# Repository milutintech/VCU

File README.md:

# VCU - Vehicle Control Unit

A professional FreeRTOS-based vehicle control unit for ESP32-S3 with a JSON/WebSocket API. [LIVI](../../LIVI) is the user interface; the VCU serves no web page of its own.

## Features

### Core Functionality
- **FreeRTOS Multi-tasking**: Three dedicated tasks for CAN communication, control logic, and web server
- **Advanced Pedal Control**: Three-zone system (Regen/Coast/Accel) with smooth torque transitions
- **CAN Bus Integration**: Manages BMS, DMC, BSC, and NLG subsystems
- **Persistent Configuration**: JSON-based flash storage with validation
- **Real-time Monitoring**: Error logging, performance metrics, and system health checks

### API
- **Always-On Web Server**: REST + WebSocket on port 80, used by LIVI
- **WebSocket Updates**: 10Hz live data streaming
- **BMS cells and faults**: see the end of this file

## Hardware

### Microcontroller
- **ESP32-S3 DevKit C1**
- Dual-core ARM @ 240 MHz
- 16 MB Flash, 8 MB SRAM

### Communication
- MCP2515 CAN Controller (SPI)
- ADS1115 16-bit ADC (I2C)
- WiFi 802.11 b/g/n

### I/O
- Dual throttle pedal inputs
- HV contactor control
- Cooling pump PWM
- Charger/inverter enable outputs
- Connector unlock interrupt

## Quick Start

### 1. Build and Upload Firmware

```bash
# Install PlatformIO
pip install platformio

# Build project
pio run

# Upload firmware
pio run --target upload
```

### 2. First-Time Setup

1. Power on the VCU
2. Look for WiFi network: `VCU_XXXXX` (XXXXX = chip ID)
3. Connect with password: `vcu12345`
4. Point LIVI at `192.168.4.1` (Settings → Vehicle → Status)

## REST API

All configuration is accessible via REST API:

### Status Endpoints
```
GET /api/status              - System status
GET /api/status/live         - Real-time vehicle data
GET /api/status/errors       - Error log
```

### Configuration Endpoints
```
GET  /api/config/driving     - Get driving config
POST /api/config/driving     - Set driving config
GET  /api/config/charging    - Get charging config
POST /api/config/charging    - Set charging config
GET  /api/config/pedal       - Get pedal zones
POST /api/config/pedal       - Set pedal zones
GET  /api/config/transition  - Get torque transitions
POST /api/config/transition  - Set torque transitions
GET  /api/config/limits      - Get speed/power limits
POST /api/config/limits      - Set limits
```

### System Endpoints
```
POST /api/system/save        - Save config to flash
POST /api/system/reset       - Factory reset
GET  /api/system/export      - Download config JSON
POST /api/system/import      - Upload config JSON
GET  /api/system/info        - System information
POST /api/system/debug       - Enable/disable debug mode
```

### CAN Monitor
```
GET /api/can/messages        - Get CAN message data
```

### WebSocket
```
ws://[IP_ADDRESS]/ws         - Real-time data stream (10Hz)
```

## Debug Mode

Debug mode prevents the VCU from entering deep sleep, useful for:
- Development and testing
- Keeping WiFi active during extended stops
- Debugging CAN communication issues

Enable via:
- API: `POST /api/system/debug {"enabled": true}`

## FreeRTOS Task Structure

### Core 0 (CAN Communication)
- **CAN Task** (Priority 1, 12KB stack)
  - CAN message RX/TX
  - Motor speed updates
  - Torque calculation
  - Temperature monitoring
  - 1ms cycle time

### Core 1 (Control & API)
- **Control Task** (Priority 1, 24KB stack)
  - State machine updates
  - Interrupt handling
  - Performance monitoring
  - 50ms cycle time

- **Web Server Task** (Priority 1, 16KB stack)
  - WiFi management
  - HTTP request handling
  - WebSocket broadcasts
  - 10ms cycle time

## Safety Features

- Input validation on all configuration changes
- Automatic fallback to safe defaults
- Error monitoring with severity levels
- System health checks
- CAN timeout detection
- Temperature monitoring
- Voltage/current limits
- Emergency stop capability

## Configuration Backup

### Export Configuration
`GET /api/system/export` returns the configuration as JSON; save it as `vcu_config.json`.

### Import Configuration
`POST /api/system/import` with the saved JSON, then `POST /api/system/save`.

## Network Configuration

### Access Point Mode (Default)
- SSID: `VCU_XXXXX` (XXXXX = chip ID)
- Password: `vcu12345`
- IP Address: `192.168.4.1`

### Station Mode
- The VCU has no API for station credentials; see `wifi_manager`
- Automatically falls back to AP if connection fails
- Reconnects automatically if WiFi drops

## Troubleshooting

### Can't Connect to WiFi
1. Check that AP mode is active (look for `VCU_` network)
2. Default password is `vcu12345`
3. Try factory reset if needed

### LIVI Can't Reach the VCU
1. Check the VCU's IP address in the serial monitor
2. Ensure LIVI's host is on the VCU's network
3. Check `http://<ip>/api/system/info` answers

### Configuration Not Saving
1. Writes are saved by the VCU itself; check the API response of `POST /api/system/save`
2. Look at the error LIVI shows under Adjustments
3. Verify flash storage isn't full

### Real-time Data Not Updating
1. Check that `/ws` accepts a connection (LIVI reconnects with backoff)
2. Confirm the link state under Settings → Vehicle → Status
3. Ensure CAN bus is connected and operational

## Development

### File Structure
```
VCU/
├── src/
│   ├── main.cpp                  - Main application
│   ├── state_manager.cpp         - State machine
│   ├── vehicle_control.cpp       - Pedal control
│   ├── can_manager.cpp           - CAN communication
│   ├── configuration.cpp         - Config management
│   ├── wifi_manager.cpp          - WiFi management
│   └── web_server.cpp            - Web server
├── include/
│   └── [corresponding headers]
├── platformio.ini                - Build configuration
└── min_spiffs.csv                - Partition table
```

### Building from Source
```bash
# Clone repository
git clone [your-repo-url]
cd VCU

# Install dependencies (automatic via PlatformIO)
pio lib install

# Build
pio run

# Upload firmware
pio run --target upload

# Monitor serial output
pio device monitor
```

## License

[Your License Here]

## Credits

Built with:
- PlatformIO
- ESP32 Arduino Framework
- ESPAsyncWebServer
- ArduinoJson
- FreeRTOS

## Support

For issues, questions, or contributions, please open an issue on GitHub.

## BMS cells and faults API (for LIVI)

- `GET /api/bms/cells` → `{ "cellsMv": [...], "balancing": [idx...], "temps": [...], "ageMs": n }`.
  Cells come from the Orion *Battery Cell Broadcast* frame (see `include/bms_cells.h`).
  `cellsMv` is empty until a valid frame has been decoded.
- `GET|POST /api/config/bms` → `{ cellId, tempId, bigEndian, checkChecksum, cellCount, tempCount, ignoreAllowFlags }`.
  `ignoreAllowFlags` (override of the BMS charge/discharge allow flags, for breakdown, trailer
  loading or debugging) is **not saved**: every boot starts with the flags enforced. The BMS current
  limits (DCL/CCL) still apply while it is on, and `BMS_FLAGS_IGNORED` stays active as a reminder.
- Live JSON `battery`: `minCell`, `maxCell` (V), `tempHigh`, `tempLow` (°C) from BMS 0x001, and
  `allow { fresh, chargeFlag, dischargeFlag, ignored, charge, discharge }` (`charge`/`discharge` =
  what the VCU acts on).
  `cellId`/`tempId` are the CAN IDs set in the Orion BMS Utility; `0` turns decoding off (default).
  Stored in its own NVS namespace, applied immediately.
- `GET /api/status/faults` → `{ "faults": [{ code, name, severity, active, count, lastSeenS }] }`.
  Every fault code raised by `FaultHandler`, INFO included (e.g. `BMS_CHARGE_NOT_ALLOWED`, `CHARGER_OVERTEMP`). `active` is edge-triggered: set on raise, cleared by `FaultHandler` once the value is back inside the hysteresis band (no time-based expiry). `count` is the number of inactive→active transitions.

## Fault handling

`FaultHandler` (`include/fault_handler.h`, `src/fault_handler.cpp`) runs every CAN-task cycle in `main.cpp`.
It is the only place that raises/clears the fault codes below and the only place that maps faults to reactions.
`ErrorMonitor` just stores them. Raising an already active fault does not log or count again.

### Faults and thresholds

Values marked *existing* come from `include/vehicle_parameters.h` and are unchanged (`INV_HIGH`/`MOT_HIGH` = 45 °C, `INV_LOW`/`MOT_LOW` = 30 °C and `FAN_ON` = 65 °C are the cooling thresholds in `StateManager`, the pump on above 45 and off below 30, the fan on above 65, and are not used for derating); the others are new and live in `FaultLimits` (`fault_handler.h`) so the safety header was not touched.

| Code | Severity | Raised when | Cleared when |
|---|---|---|---|
| `BMS_TIMEOUT` | ERROR | no BMS frame (0x010) for > 1500 ms (*existing* `Timing::BMS_TIMEOUT_MS`) | a BMS frame is fresh again |
| `DMC_TIMEOUT` | CRITICAL | in RUN, no DMC frame (0x258/0x259/0x458) for > 500 ms (new) | frame fresh again, or leaving RUN |
| `BSC_TIMEOUT` | WARNING | no BSC status frame for > 1500 ms (new) | frame fresh again |
| `NLG_TIMEOUT` | WARNING | in CHARGING, no NLG frame for > 1500 ms (new) | frame fresh again, or leaving CHARGING |
| `CHARGER_OVERTEMP` | INFO | in CHARGING, charger cooling plate > 85 °C (new; the charger itself is good to 95 °C) | plate <= 80 °C, or leaving CHARGING |
| `BATTERY_UNDERVOLTAGE` | ERROR | pack < 300 V (`Battery::MIN_VOLTAGE`), BMS data fresh | pack >= 305 V (+5 V, new) |
| `BMS_DISCHARGE_NOT_ALLOWED` | CRITICAL | in RUN, BMS discharge flag (0x001 byte 6 bit 1) off or no 0x001 frame for > 1600 ms, override off | flag on again, or leaving RUN |
| `BMS_CHARGE_NOT_ALLOWED` | INFO | in CHARGING, BMS charge flag (0x001 byte 6 bit 0) off or frame missing, override off | flag on again, or leaving CHARGING |
| `BMS_FLAGS_IGNORED` | WARNING | allow-flag override on (`ignoreAllowFlags`) | override off (or restart) |
| `BATTERY_OVERVOLTAGE` | CRITICAL | pack > 422 V (`Battery::OVERVOLTAGE`), BMS data fresh | pack <= 417 V (-5 V, new) |
| `INVERTER_OVERTEMP` | ERROR | inverter > 100 °C (new `TEMP_DERATE_C`); CRITICAL above 105 °C (new `TEMP_CUTOFF_C`) | inverter < 95 °C (-5 °C, new) |
| `MOTOR_OVERTEMP` | ERROR | motor > 100 °C (new `TEMP_DERATE_C`); CRITICAL above 105 °C (new `TEMP_CUTOFF_C`) | motor < 95 °C (-5 °C, new) |

Nodes that never sent anything are timed from boot (BMS, BSC) or from entering the state that needs them (DMC, NLG), so an unpowered node in standby does not raise a fault. Temperature faults are evaluated only after the first DMC frame, voltage faults only while BMS data is fresh.
Not wired yet (no source signal in the firmware): `BATTERY_OVERCURRENT`, `DMC_ERROR`, `SOC_OUT_OF_RANGE`, precharge and charger codes.

### Reactions

Applied in `canTask` (`main.cpp`) in RUN state; the fault reaction is the minimum over all active faults.

| Active fault | Reaction |
|---|---|
| `INVERTER_OVERTEMP` / `MOTOR_OVERTEMP` | torque request x 0.5 (drive and regen); x 0 above 105 °C |
| `BATTERY_UNDERVOLTAGE` | torque request x 0.5 |
| `BATTERY_OVERVOLTAGE` | torque request x 0 |
| `BMS_TIMEOUT` | torque request x 0 |
| any active CRITICAL fault (`DMC_TIMEOUT`, `BATTERY_OVERVOLTAGE`, overtemp above 105 °C) | torque x 0 and DMC enable bit forced off |
| `BSC_TIMEOUT`, `NLG_TIMEOUT`, `CHARGER_OVERTEMP` | log/report only (the charger reduces its own power) |

The allow flags also act directly in `CANManager`, in every state: discharge not allowed sets the DMC
drive current limit to 0; charge not allowed sets the charger DC current and the DMC regen current
limit to 0. Not latched: current flows again as soon as the BMS sets the flag again.
Regen torque itself is also not requested while charge is not allowed or the BMS charge limit
(CCL) is 0 A: the DMC's 0 A generator current limit alone still let some current into a full
pack (Orion P0A06). The pedal's regen zone then behaves like coasting.
With max SOC at 100 % the SOC is not checked at all: charging continues until the plug is pulled,
governed only by the BMS charge limit (CCL) and charge flag.

Reactions are not latched: they release automatically once the fault clears. `isSystemHealthy()` now reports unhealthy while a CRITICAL fault is active (instead of whenever any critical line was ever logged). `/api/status/faults` output shape is unchanged. CAN IDs and task timing are unchanged.

- `GET /api/system/limits` → the limits LIVI uses for gauges and slider ranges: `maxRpm`
  (`VehicleParams::Motor::MAX_RPM`, the one applied in `CANManager`), `maxTorque`, `maxSoc`,
  `chargeCurrent` (min/max), `motorTemp`/`inverterTemp` (`derate`, `cutoff`),
  `packVoltage` (min/max), `chargerTempMax`.

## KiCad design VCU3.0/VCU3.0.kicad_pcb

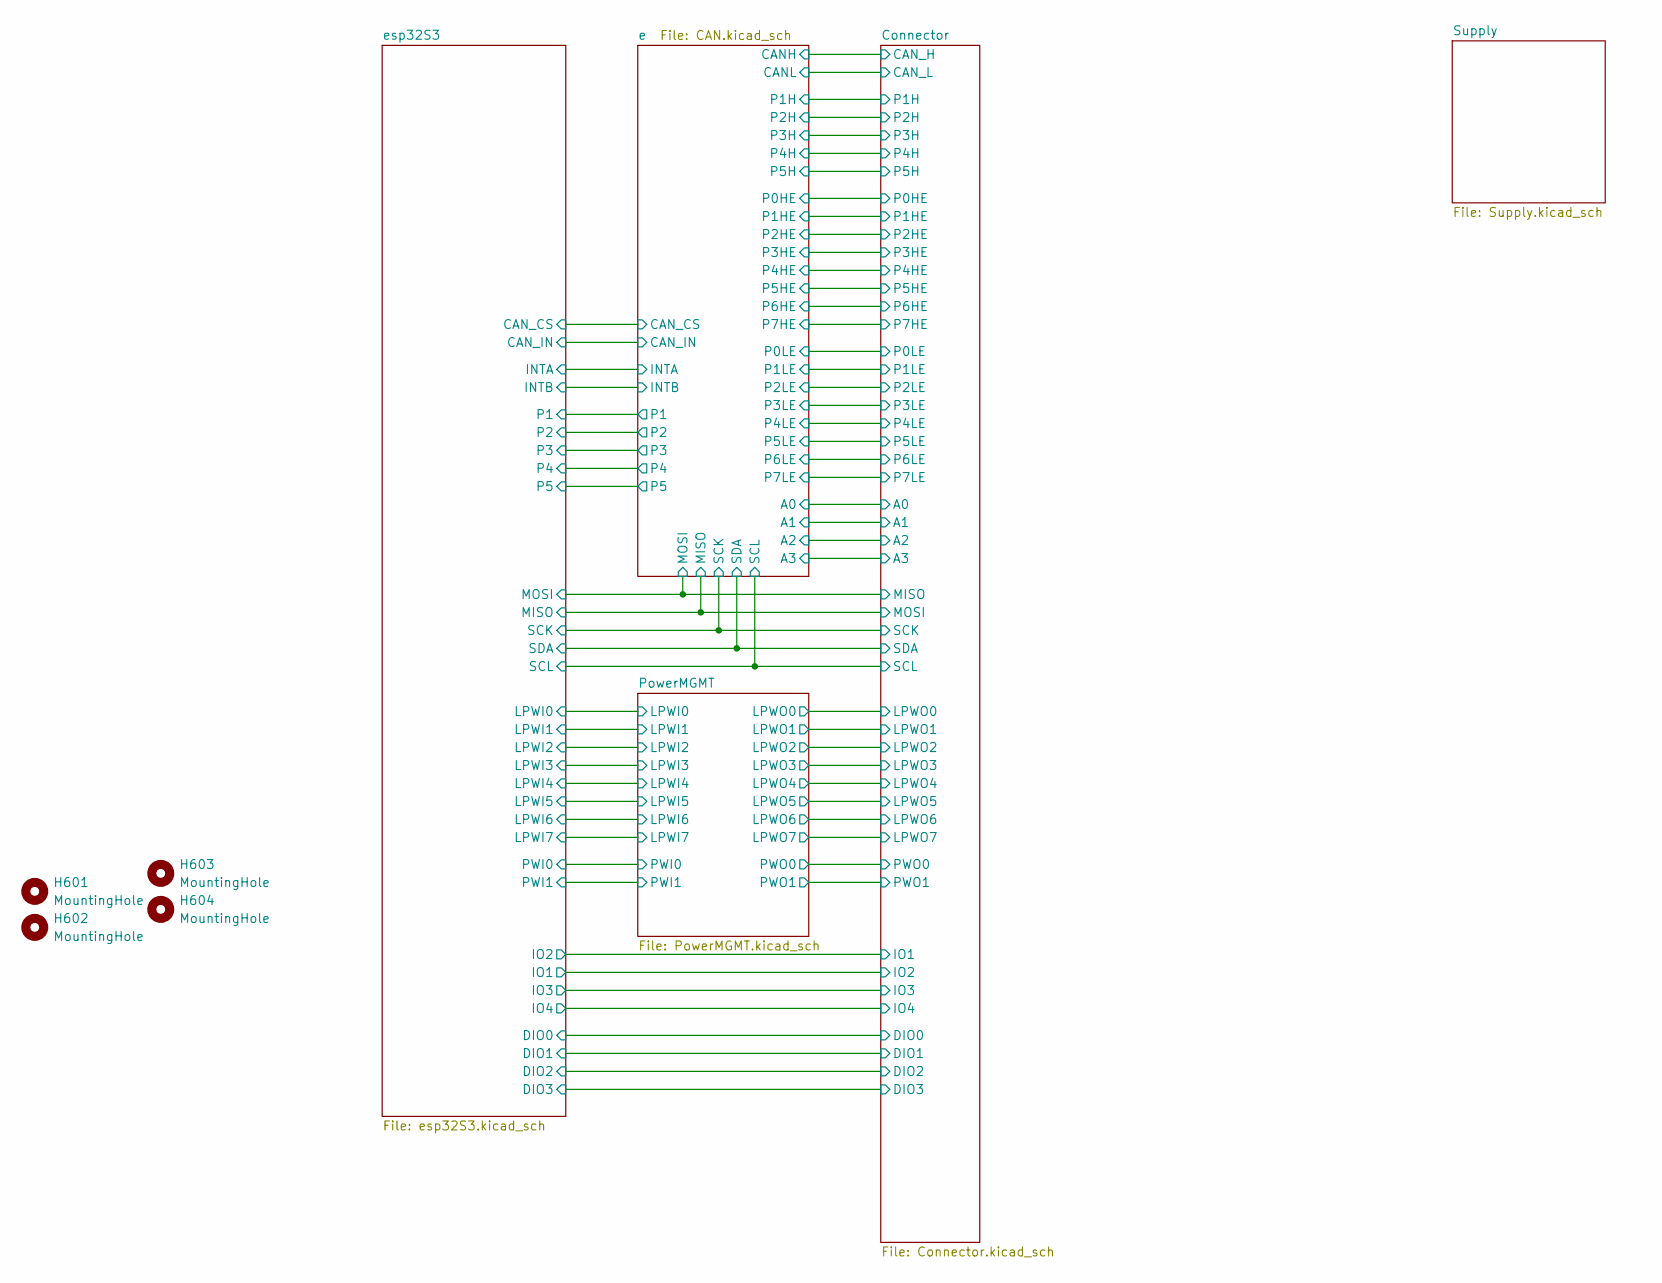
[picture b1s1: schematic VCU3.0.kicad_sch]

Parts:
H601, H602, H603, H604: MountingHole; MountingHole_3.2mm_M3_DIN965

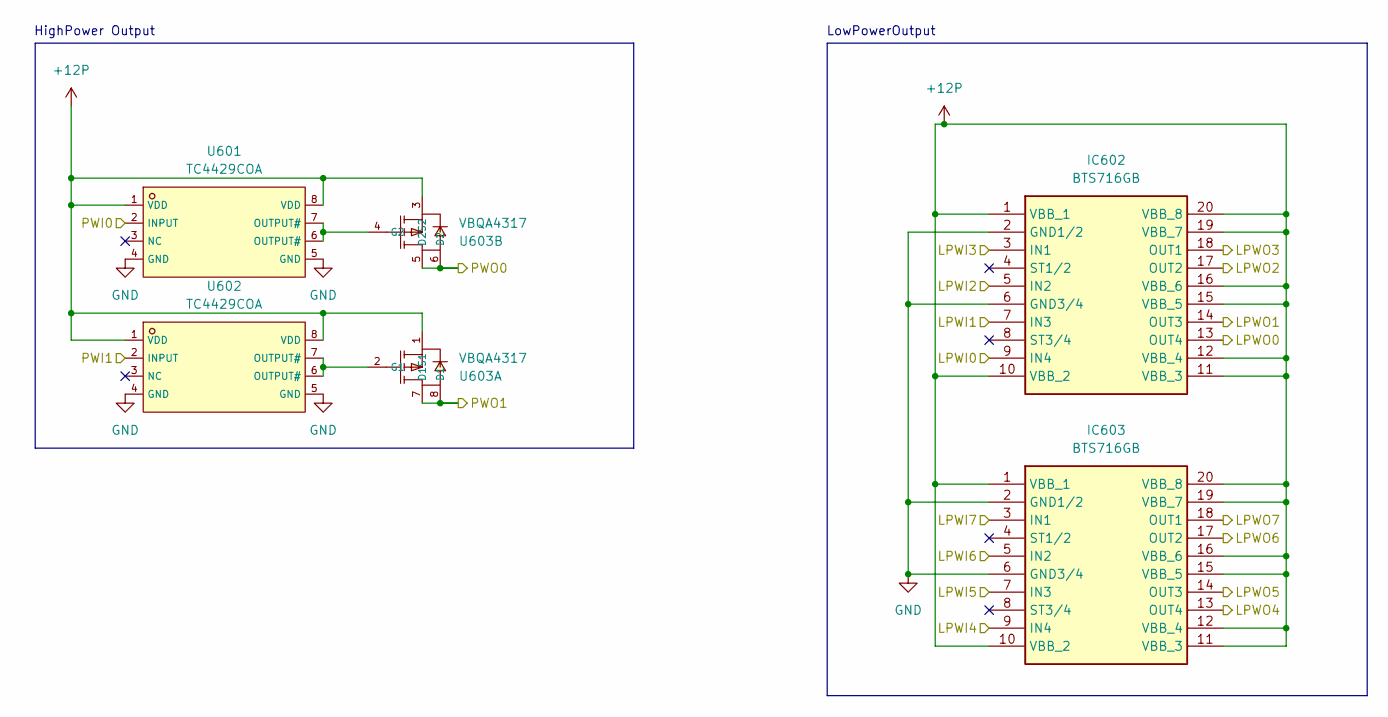
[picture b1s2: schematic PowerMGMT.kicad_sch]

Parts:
IC602, IC603: BTS716GB; SOIC127P1030X265-20N; Mouser Part Number 726-BTS716GB
U601, U602: TC4429COA; SOIC-8_L4.9-W3.9-P1.27-LS6.0-BL; LCSC C636901
U603: VBQA4317; PDFN-8_L5.9-W5.2-P1.27-LS6.2-BL-1; LCSC C7541192

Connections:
+12P: IC602.1 (VBB_1), IC602.10 (VBB_2), IC602.11 (VBB_3), IC602.12 (VBB_4), IC602.15 (VBB_5), IC602.16 (VBB_6), IC602.19 (VBB_7), IC602.20 (VBB_8), IC603.1 (VBB_1), IC603.10 (VBB_2), IC603.11 (VBB_3), IC603.12 (VBB_4), IC603.15 (VBB_5), IC603.16 (VBB_6), IC603.19 (VBB_7), IC603.20 (VBB_8), U601.1 (VDD), U601.8 (VDD), U602.1 (VDD), U602.8 (VDD), U603.1 (S1), U603.3 (S2); also elsewhere on the board
/Connector/LPWO0: IC602.13 (OUT4); also elsewhere on the board
/Connector/LPWO1: IC602.14 (OUT3); also elsewhere on the board
/Connector/LPWO2: IC602.17 (OUT2); also elsewhere on the board
/Connector/LPWO3: IC602.18 (OUT1); also elsewhere on the board
/Connector/LPWO4: IC603.13 (OUT4); also elsewhere on the board
/Connector/LPWO5: IC603.14 (OUT3); also elsewhere on the board
/Connector/LPWO6: IC603.17 (OUT2); also elsewhere on the board
/Connector/LPWO7: IC603.18 (OUT1); also elsewhere on the board
/Connector/PWO0: U603.5 (D2), U603.6 (D2); also elsewhere on the board
/Connector/PWO1: U603.7 (D1), U603.8 (D1); also elsewhere on the board
/PowerMGMT/LPWI0: IC602.9 (IN4); also elsewhere on the board
/PowerMGMT/LPWI1: IC602.7 (IN3); also elsewhere on the board
/PowerMGMT/LPWI2: IC602.5 (IN2); also elsewhere on the board
/PowerMGMT/LPWI3: IC602.3 (IN1); also elsewhere on the board
/PowerMGMT/LPWI4: IC603.9 (IN4); also elsewhere on the board
/PowerMGMT/LPWI5: IC603.7 (IN3); also elsewhere on the board
/PowerMGMT/LPWI6: IC603.5 (IN2); also elsewhere on the board
/PowerMGMT/LPWI7: IC603.3 (IN1); also elsewhere on the board
/PowerMGMT/PWI0: U601.2 (INPUT); also elsewhere on the board
/PowerMGMT/PWI1: U602.2 (INPUT); also elsewhere on the board
GND: IC602.2 (GND1/2), IC602.6 (GND3/4), IC603.2 (GND1/2), IC603.6 (GND3/4), U601.4 (GND), U601.5 (GND), U602.4 (GND), U602.5 (GND); also elsewhere on the board
unnamed: U602.6 (OUTPUT#), U602.7 (OUTPUT#), U603.2 (G1)
unnamed: U601.6 (OUTPUT#), U601.7 (OUTPUT#), U603.4 (G2)

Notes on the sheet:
HighPower Output
LowPowerOutput

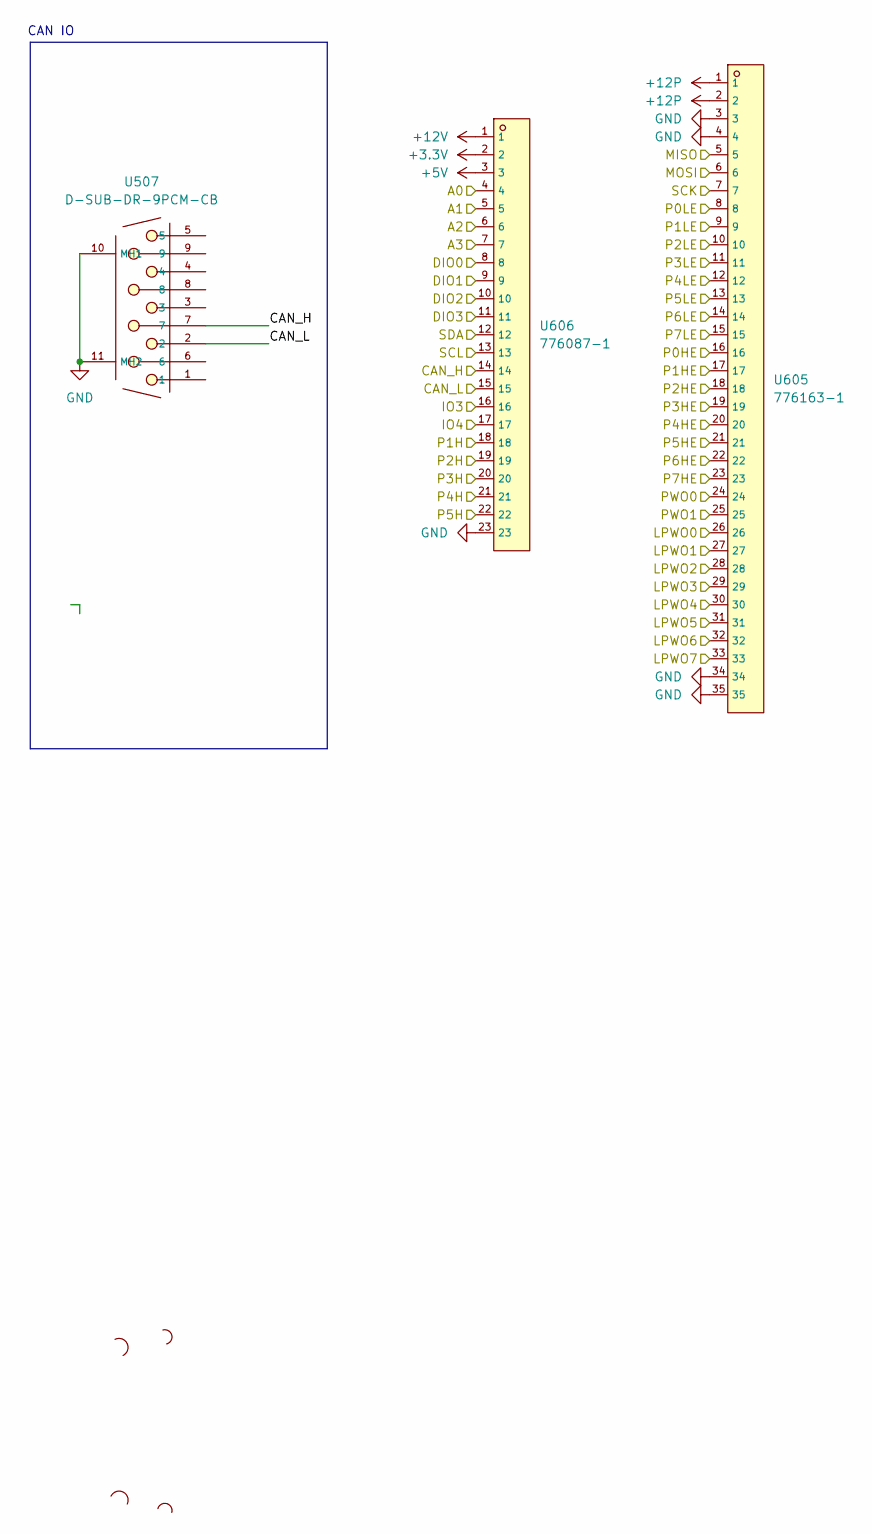
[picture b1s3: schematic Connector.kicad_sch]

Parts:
U507: D-SUB-DR-9PCM-CB; DB9-TH_D-SUB-DR-9PCM-CB; LCSC C19077337
U605: 776163-1; CONN-TH_776163-1; LCSC C412117
U606: 776087-1; CONN-TH_776087-1; LCSC C378893

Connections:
+3.3V: U606.2; also elsewhere on the board
+5V: U606.3; also elsewhere on the board
+12P: U605.1, U605.2; also elsewhere on the board
+12V: U606.1; also elsewhere on the board
/Connector/A0: U606.4; also elsewhere on the board
/Connector/A1: U606.5; also elsewhere on the board
/Connector/A2: U606.6; also elsewhere on the board
/Connector/A3: U606.7; also elsewhere on the board
/Connector/CAN_H: U507.7, U606.14; also elsewhere on the board
/Connector/CAN_L: U507.2, U606.15; also elsewhere on the board
/Connector/DIO0: U606.8; also elsewhere on the board
/Connector/DIO1: U606.9; also elsewhere on the board
/Connector/DIO2: U606.10; also elsewhere on the board
/Connector/DIO3: U606.11; also elsewhere on the board
/Connector/IO3: U606.16; also elsewhere on the board
/Connector/IO4: U606.17; also elsewhere on the board
/Connector/LPWO0: U605.26; also elsewhere on the board
/Connector/LPWO1: U605.27; also elsewhere on the board
/Connector/LPWO2: U605.28; also elsewhere on the board
/Connector/LPWO3: U605.29; also elsewhere on the board
/Connector/LPWO4: U605.30; also elsewhere on the board
/Connector/LPWO5: U605.31; also elsewhere on the board
/Connector/LPWO6: U605.32; also elsewhere on the board
/Connector/LPWO7: U605.33; also elsewhere on the board
/Connector/MISO: U605.5; also elsewhere on the board
/Connector/MOSI: U605.6; also elsewhere on the board
/Connector/P0HE: U605.16; also elsewhere on the board
/Connector/P0LE: U605.8; also elsewhere on the board
/Connector/P1H: U606.18; also elsewhere on the board
/Connector/P1HE: U605.17; also elsewhere on the board
/Connector/P1LE: U605.9; also elsewhere on the board
/Connector/P2H: U606.19; also elsewhere on the board
/Connector/P2HE: U605.18; also elsewhere on the board
/Connector/P2LE: U605.10; also elsewhere on the board
/Connector/P3H: U606.20; also elsewhere on the board
/Connector/P3HE: U605.19; also elsewhere on the board
/Connector/P3LE: U605.11; also elsewhere on the board
/Connector/P4H: U606.21; also elsewhere on the board
/Connector/P4HE: U605.20; also elsewhere on the board
/Connector/P4LE: U605.12; also elsewhere on the board
/Connector/P5H: U606.22; also elsewhere on the board
/Connector/P5HE: U605.21; also elsewhere on the board
/Connector/P5LE: U605.13; also elsewhere on the board
/Connector/P6HE: U605.22; also elsewhere on the board
/Connector/P6LE: U605.14; also elsewhere on the board
/Connector/P7HE: U605.23; also elsewhere on the board
/Connector/P7LE: U605.15; also elsewhere on the board
/Connector/PWO0: U605.24; also elsewhere on the board
/Connector/PWO1: U605.25; also elsewhere on the board
/Connector/SCK: U605.7; also elsewhere on the board
/Connector/SCL: U606.13; also elsewhere on the board
/Connector/SDA: U606.12; also elsewhere on the board
GND: U507.10 (MH1), U507.11 (MH2), U605.3, U605.4, U605.34, U605.35, U606.23; also elsewhere on the board

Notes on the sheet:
CAN IO

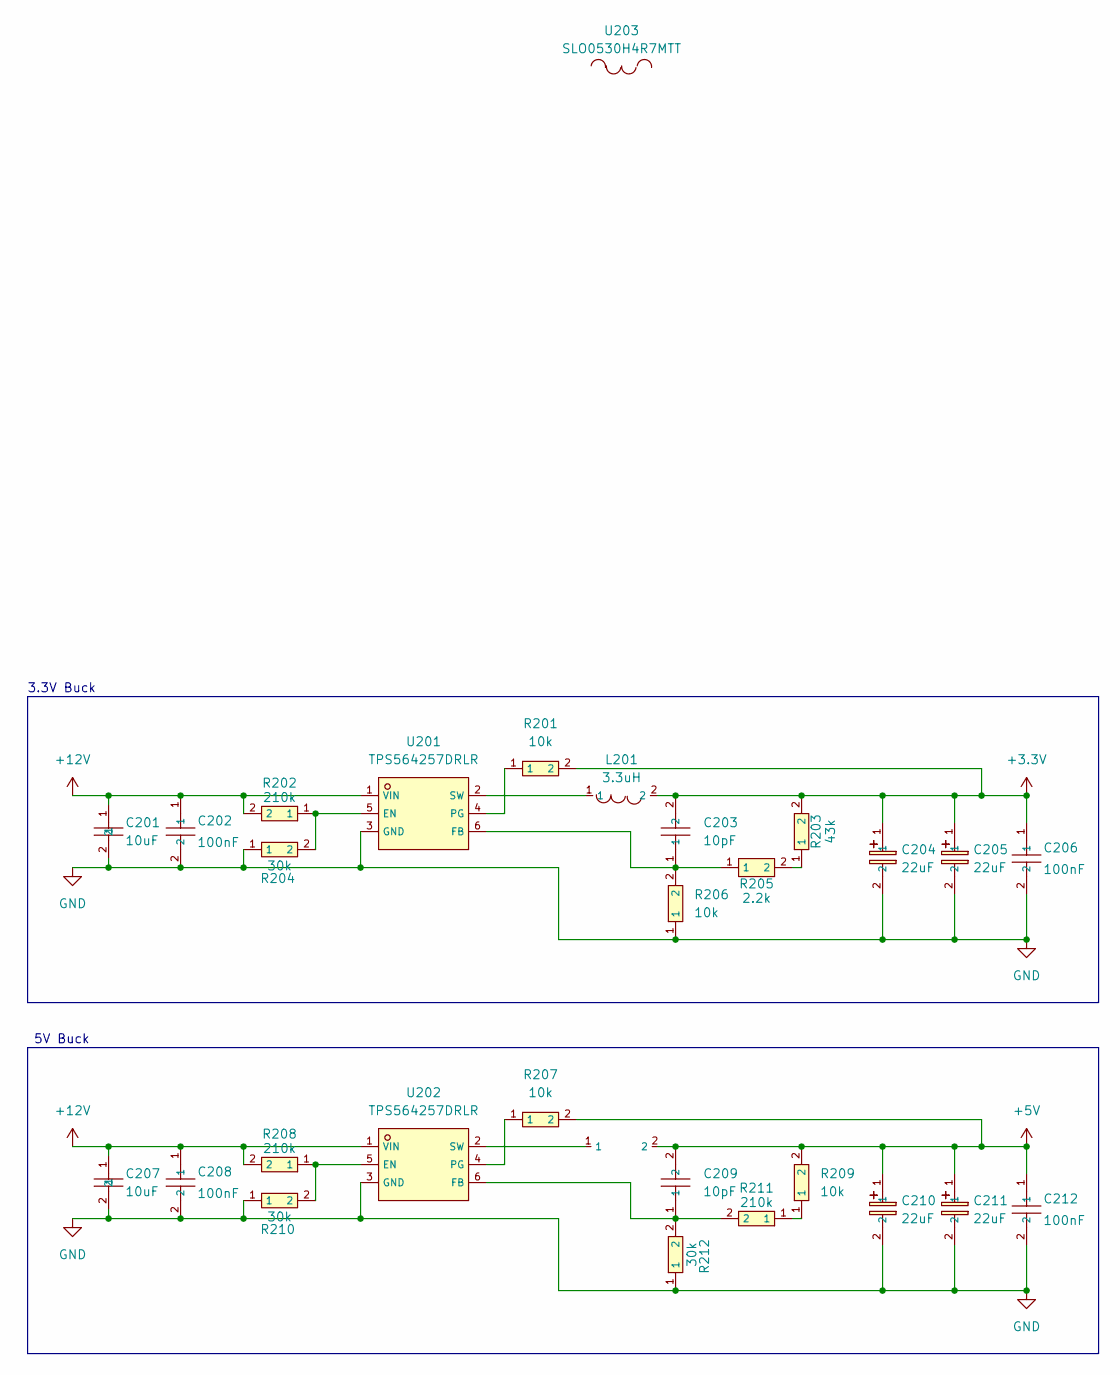
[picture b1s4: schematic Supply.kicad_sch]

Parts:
C201, C207: 10uF; C0805; LCSC C1713
C202, C206, C208, C212: 100nF; C0603; LCSC C14663
C203, C209: 10pF; C0603; LCSC C325468
C204, C205, C210, C211: 22uF; CAP-SMD_L7.3-W4.3-L-FD; LCSC C347543
L201: 3.3uH; IND-SMD_L7.3-W6.6; LCSC C351116
R201, R206, R207, R209: 10k; R0603; LCSC C98220
R202, R208, R211: 210k; R0603; LCSC C217875
R203: 43k; R0603; LCSC C137719
R204, R210, R212: 30k; R0603; LCSC C113302
R205: 2.2k; R0603; LCSC C227479
U201, U202: TPS564257DRLR; SOT-563-6_L1.6-W1.2-P0.5-LS1.6-BR; LCSC C19272233
U203: SLO0530H4R7MTT; IND-SMD_L5.4-W5.2; LCSC C325964

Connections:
+3.3V: C203.2, C204.1, C205.1, C206.1, L201.2, R201.2, R203.2; also elsewhere on the board
+5V: C209.2, C210.1, C211.1, C212.1, R207.2, R209.2, U203.2; also elsewhere on the board
+12V: C201.1, C202.1, C207.1, C208.1, R202.2, R208.2, U201.1 (VIN), U202.1 (VIN); also elsewhere on the board
GND: C201.2, C202.2, C204.2, C205.2, C206.2, C207.2, C208.2, C210.2, C211.2, C212.2, R204.1, R206.1, R210.1, R212.1, U201.3 (GND), U202.3 (GND); also elsewhere on the board
unnamed: R203.1, R205.2
unnamed: R209.1, R211.1
unnamed: R202.1, R204.2, U201.5 (EN)
unnamed: C203.1, R205.1, R206.2, U201.6 (FB)
unnamed: R201.1, U201.4 (PG)
unnamed: L201.1, U201.2 (SW)
unnamed: R208.1, R210.2, U202.5 (EN)
unnamed: C209.1, R211.2, R212.2, U202.6 (FB)
unnamed: R207.1, U202.4 (PG)
unnamed: U202.2 (SW), U203.1

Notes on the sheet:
3.3V Buck
5V Buck

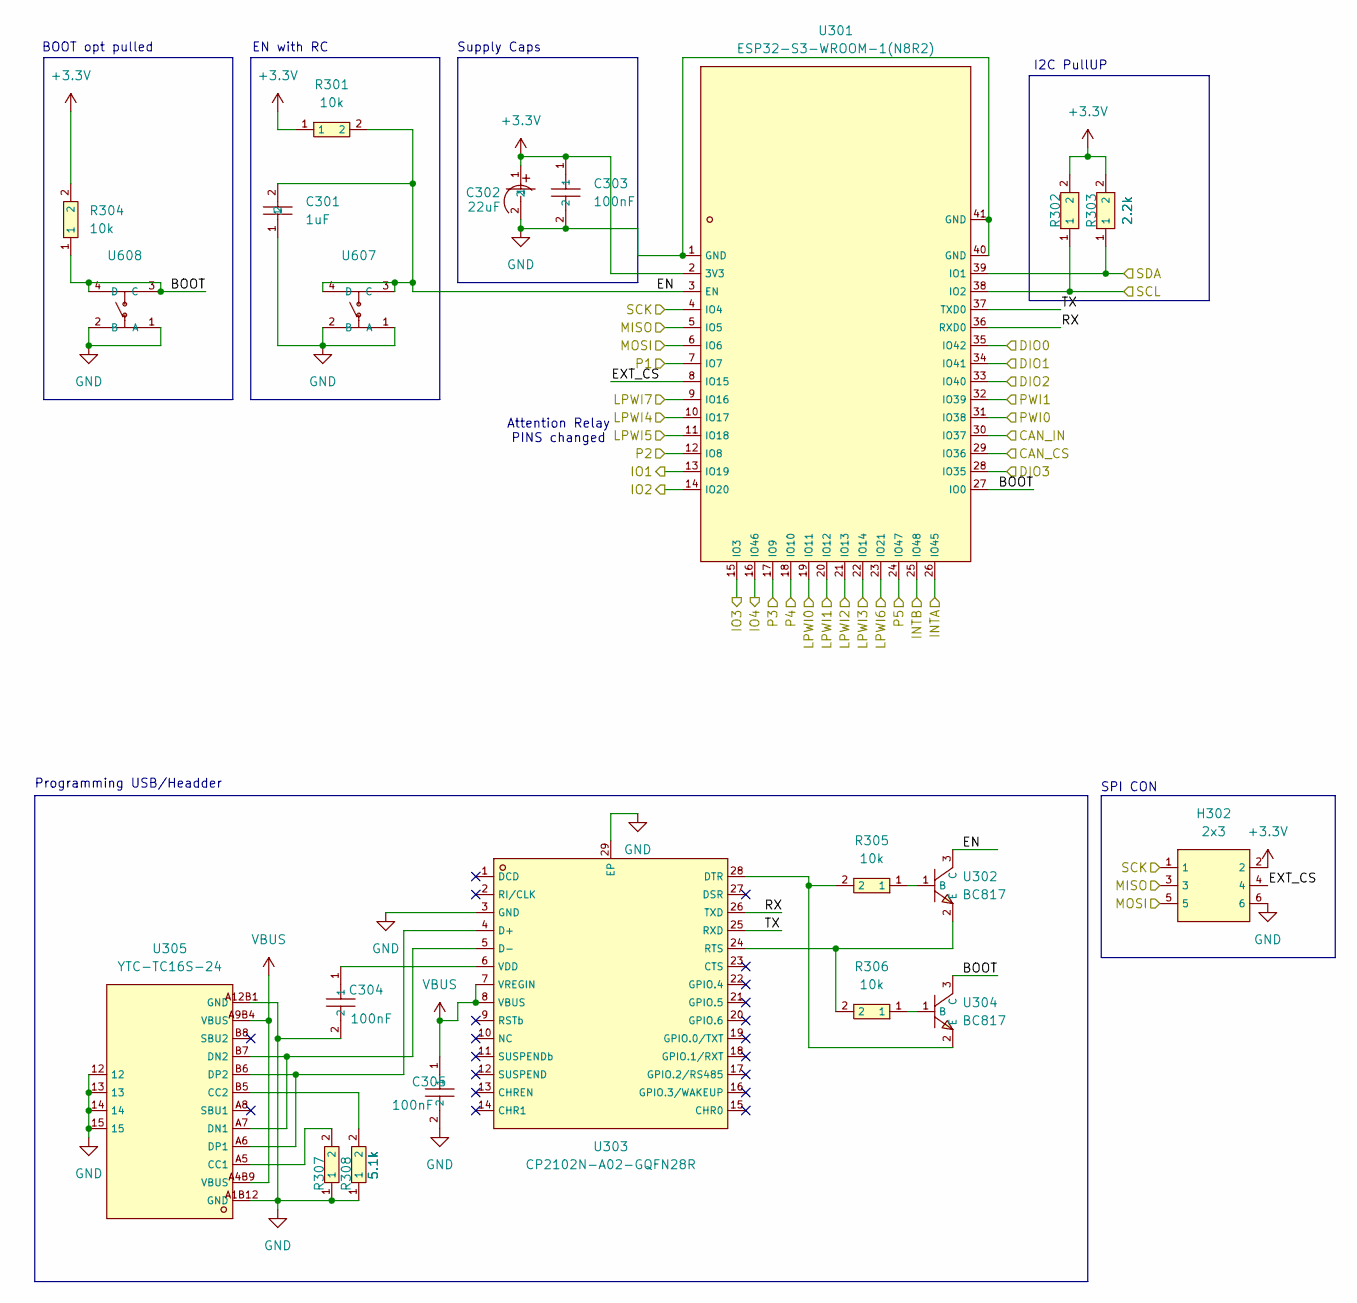
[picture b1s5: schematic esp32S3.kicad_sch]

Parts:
C301: 1uF; C0805; LCSC C28323
C302: 22uF; CAP-SMD_BD4.0-L4.3-W4.3-LS5.1-FD; LCSC C131114
C303, C304, C305: 100nF; C0603; LCSC C14663
H302: 2x3; HDR-TH_6P-P2.54-V-M-R2-C3-S2.54-1; LCSC C65114
R301, R304, R305, R306: 10k; R0603; LCSC C98220
R302, R303: 2.2k; R0603; LCSC C227479
R307, R308: 5.1k; R0603; LCSC C186203
U301: ESP32-S3-WROOM-1(N8R2); WIRELM-SMD_ESP32-S3-WROOM-1; LCSC C2913204
U302, U304: BC817; SOT-23-3_L2.9-W1.3-P1.90-LS2.4-BR; LCSC C549442
U303: CP2102N-A02-GQFN28R; QFN-28_L5.0-W5.0-P0.50-TL-EP3.3; LCSC C964632
U305: YTC-TC16S-24; USB-C-SMD_YTC-TC16S-24; LCSC C2927291
U607, U608: HX-6X6X7_3-TP_FT_SQUARE_BUTTON; SW-SMD_4P-L6.0-W6.0-P4.50-LS9.0-H7.3; LCSC C49234152

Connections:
+3.3V: C302.1, C303.1, H302.2, R301.1, R302.2, R303.2, R304.2, U301.2 (3V3); also elsewhere on the board
/Connector/DIO0: U301.35 (IO42); also elsewhere on the board
/Connector/DIO1: U301.34 (IO41); also elsewhere on the board
/Connector/DIO2: U301.33 (IO40); also elsewhere on the board
/Connector/DIO3: U301.28 (IO35); also elsewhere on the board
/Connector/IO3: U301.15 (IO3); also elsewhere on the board
/Connector/IO4: U301.16 (IO46); also elsewhere on the board
/Connector/MISO: H302.5, U301.6 (IO6); also elsewhere on the board
/Connector/MOSI: H302.3, U301.5 (IO5); also elsewhere on the board
/Connector/SCK: H302.1, U301.4 (IO4); also elsewhere on the board
/Connector/SCL: R302.1, U301.38 (IO2); also elsewhere on the board
/Connector/SDA: R303.1, U301.39 (IO1); also elsewhere on the board
/PowerMGMT/LPWI0: U301.19 (IO11); also elsewhere on the board
/PowerMGMT/LPWI1: U301.20 (IO12); also elsewhere on the board
/PowerMGMT/LPWI2: U301.21 (IO13); also elsewhere on the board
/PowerMGMT/LPWI3: U301.22 (IO14); also elsewhere on the board
/PowerMGMT/LPWI4: U301.10 (IO17); also elsewhere on the board
/PowerMGMT/LPWI5: U301.11 (IO18); also elsewhere on the board
/PowerMGMT/LPWI6: U301.23 (IO21); also elsewhere on the board
/PowerMGMT/LPWI7: U301.9 (IO16); also elsewhere on the board
/PowerMGMT/PWI0: U301.31 (IO38); also elsewhere on the board
/PowerMGMT/PWI1: U301.32 (IO39); also elsewhere on the board
/e/CAN_CS: U301.29 (IO36); also elsewhere on the board
/e/CAN_IN: U301.30 (IO37); also elsewhere on the board
/e/INTA: U301.26 (IO45); also elsewhere on the board
/e/INTB: U301.25 (IO48); also elsewhere on the board
/e/P1: U301.7 (IO7); also elsewhere on the board
/e/P2: U301.12 (IO8); also elsewhere on the board
/e/P3: U301.17 (IO9); also elsewhere on the board
/e/P4: U301.18 (IO10); also elsewhere on the board
/e/P5: U301.24 (IO47); also elsewhere on the board
/esp32S3/BOOT: R304.1, U301.27 (IO0), U304.3 (C), U608.3 (C), U608.4 (D)
/esp32S3/EN: C301.2, R301.2, U301.3 (EN), U302.3 (C), U607.3 (C), U607.4 (D)
/esp32S3/EXT_CS: H302.4, U301.8 (IO15)
/esp32S3/IO1: U301.13 (IO19)
/esp32S3/IO2: U301.14 (IO20)
/esp32S3/RX: U301.36 (RXD0), U303.26 (TXD)
/esp32S3/TX: U301.37 (TXD0), U303.25 (RXD)
GND: C301.1, C302.2, C303.2, C304.2, C305.2, H302.6, R307.1, R308.1, U301.1 (GND), U301.40 (GND), U301.41 (GND), U303.3 (GND), U303.29 (EP), U305.12, U305.13, U305.14, U305.15, U305.A1B12 (GND), U305.A12B1 (GND), U607.1 (A), U607.2 (B), U608.1 (A), U608.2 (B); also elsewhere on the board
unnamed: R305.1, U302.1 (B)
unnamed: R306.2, U302.2 (E), U303.24 (RTS)
unnamed: U303.4 (D+), U305.A6 (DP1), U305.B6 (DP2)
unnamed: U303.5 (D-), U305.A7 (DN1), U305.B7 (DN2)
unnamed: R305.2, U303.28 (DTR), U304.2 (E)
unnamed: C304.1, U303.6 (VDD)
unnamed: R306.1, U304.1 (B)
unnamed: R307.2, U305.A5 (CC1)
unnamed: R308.2, U305.B5 (CC2)
VBUS: C305.1, U303.7 (VREGIN), U303.8 (VBUS), U305.A4B9 (VBUS), U305.A9B4 (VBUS)

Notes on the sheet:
EN with RC
Programming USB/Headder
I2C PullUP
Supply Caps
SPI CON
Attention Relay PINS changed
BOOT opt pulled

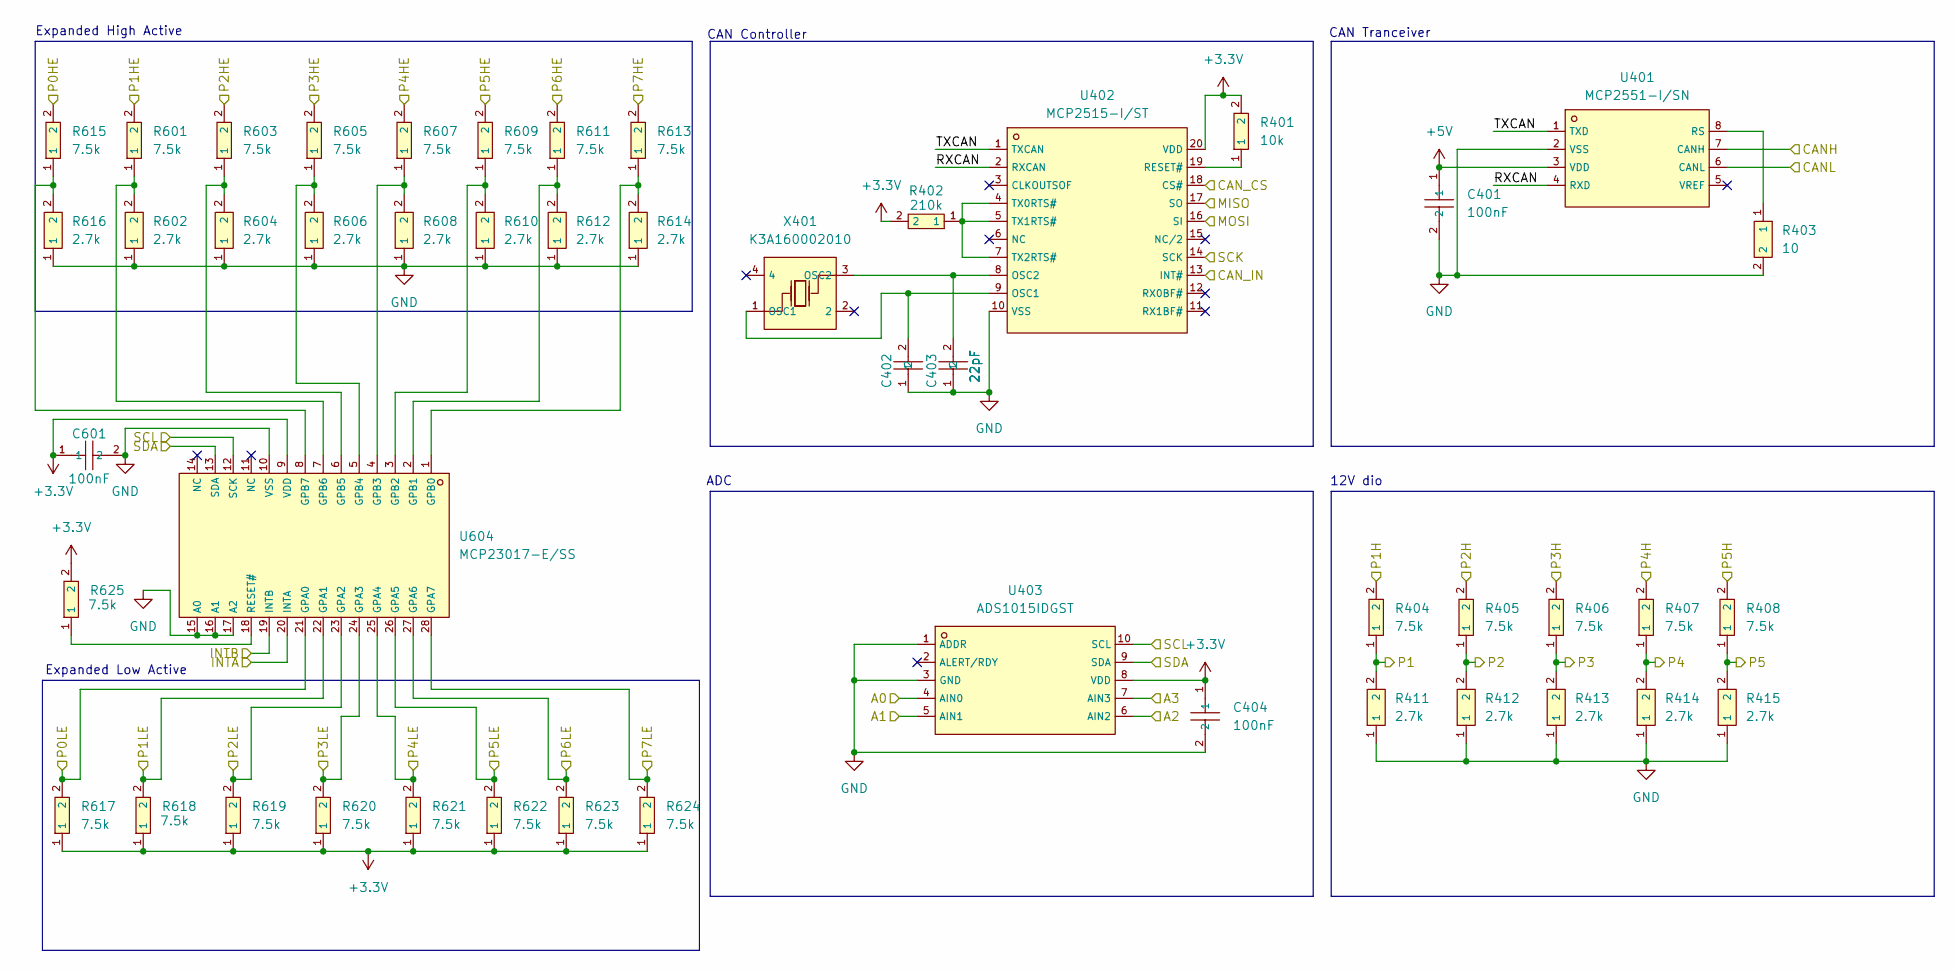
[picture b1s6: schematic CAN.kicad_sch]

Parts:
C401, C404, C601: 100nF; C0603; LCSC C14663
C402, C403: 22pF; C0603; LCSC C105620
R401: 10k; R0603; LCSC C98220
R402: 210k; R0603; LCSC C217875
R403: 10; R0603; LCSC C403411
R404, R405, R406, R407, R408, R601, R603, R605, R607, R609, R611, R613, R615, R617, R618, R619, R620, R621, R622, R623, R624, R625: 7.5k; R0603; LCSC C328377
R411, R412, R413, R414, R415, R602, R604, R606, R608, R610, R612, R614, R616: 2.7k; R0603; LCSC C3017728
U401: MCP2551-I/SN; SOIC-8_L4.9-W3.9-P1.27-LS6.0-BL; LCSC C7376
U402: MCP2515-I/ST; TSSOP-20_L6.5-W4.4-P0.65-LS6.4-BL; LCSC C15193
U403: ADS1015IDGST; VSSOP-10_L3.0-W3.0-P0.50-LS4.9-BL; LCSC C701606
U604: MCP23017-E/SS; SSOP-28_L10.2-W5.3-P0.65-LS7.8-BL; LCSC C506653
X401: K3A160002010; CRYSTAL-SMD_4P-L3.2-W2.5-BL; LCSC C368736

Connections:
+3.3V: C404.1, C601.1, R401.2, R402.2, R617.1, R618.1, R619.1, R620.1, R621.1, R622.1, R623.1, R624.1, R625.2, U402.20 (VDD), U403.8 (VDD), U604.9 (VDD); also elsewhere on the board
+5V: C401.1, U401.3 (VDD); also elsewhere on the board
/Connector/A0: U403.4 (AIN0); also elsewhere on the board
/Connector/A1: U403.5 (AIN1); also elsewhere on the board
/Connector/A2: U403.6 (AIN2); also elsewhere on the board
/Connector/A3: U403.7 (AIN3); also elsewhere on the board
/Connector/CAN_H: U401.7 (CANH); also elsewhere on the board
/Connector/CAN_L: U401.6 (CANL); also elsewhere on the board
/Connector/MISO: U402.16 (SI); also elsewhere on the board
/Connector/MOSI: U402.17 (SO); also elsewhere on the board
/Connector/P0HE: R615.2; also elsewhere on the board
/Connector/P0LE: R617.2, U604.21 (GPA0); also elsewhere on the board
/Connector/P1H: R404.2; also elsewhere on the board
/Connector/P1HE: R601.2; also elsewhere on the board
/Connector/P1LE: R618.2, U604.22 (GPA1); also elsewhere on the board
/Connector/P2H: R405.2; also elsewhere on the board
/Connector/P2HE: R603.2; also elsewhere on the board
/Connector/P2LE: R619.2, U604.23 (GPA2); also elsewhere on the board
/Connector/P3H: R406.2; also elsewhere on the board
/Connector/P3HE: R605.2; also elsewhere on the board
/Connector/P3LE: R620.2, U604.24 (GPA3); also elsewhere on the board
/Connector/P4H: R407.2; also elsewhere on the board
/Connector/P4HE: R607.2; also elsewhere on the board
/Connector/P4LE: R621.2, U604.25 (GPA4); also elsewhere on the board
/Connector/P5H: R408.2; also elsewhere on the board
/Connector/P5HE: R609.2; also elsewhere on the board
/Connector/P5LE: R622.2, U604.26 (GPA5); also elsewhere on the board
/Connector/P6HE: R611.2; also elsewhere on the board
/Connector/P6LE: R623.2, U604.27 (GPA6); also elsewhere on the board
/Connector/P7HE: R613.2; also elsewhere on the board
/Connector/P7LE: R624.2, U604.28 (GPA7); also elsewhere on the board
/Connector/SCK: U402.14 (SCK); also elsewhere on the board
/Connector/SCL: U403.10 (SCL), U604.12 (SCK); also elsewhere on the board
/Connector/SDA: U403.9 (SDA), U604.13 (SDA); also elsewhere on the board
/e/CAN_CS: U402.18 (CS#); also elsewhere on the board
/e/CAN_IN: U402.13 (INT#); also elsewhere on the board
/e/INTA: U604.20 (INTA); also elsewhere on the board
/e/INTB: U604.19 (INTB); also elsewhere on the board
/e/P1: R404.1, R411.2; also elsewhere on the board
/e/P2: R405.1, R412.2; also elsewhere on the board
/e/P3: R406.1, R413.2; also elsewhere on the board
/e/P4: R407.1, R414.2; also elsewhere on the board
/e/P5: R408.1, R415.2; also elsewhere on the board
/e/RXCAN: U401.4 (RXD), U402.2 (RXCAN)
/e/TXCAN: U401.1 (TXD), U402.1 (TXCAN)
GND: C401.2, C402.1, C403.1, C404.2, C601.2, R403.2, R411.1, R412.1, R413.1, R414.1, R415.1, R602.1, R604.1, R606.1, R608.1, R610.1, R612.1, R614.1, R616.1, U401.2 (VSS), U402.10 (VSS), U403.1 (ADDR), U403.3 (GND), U604.10 (VSS), U604.15 (A0), U604.16 (A1), U604.17 (A2); also elsewhere on the board
unnamed: R403.1, U401.8 (RS)
unnamed: C402.2, U402.9 (OSC1), X401.1 (OSC1)
unnamed: C403.2, U402.8 (OSC2), X401.3 (OSC2)
unnamed: R401.1, U402.19 (RESET#)
unnamed: R402.1, U402.4 (TX0RTS#), U402.5 (TX1RTS#), U402.7 (TX2RTS#)
unnamed: R613.1, R614.2, U604.1 (GPB0)
unnamed: R611.1, R612.2, U604.2 (GPB1)
unnamed: R609.1, R610.2, U604.3 (GPB2)
unnamed: R607.1, R608.2, U604.4 (GPB3)
unnamed: R605.1, R606.2, U604.5 (GPB4)
unnamed: R603.1, R604.2, U604.6 (GPB5)
unnamed: R601.1, R602.2, U604.7 (GPB6)
unnamed: R615.1, R616.2, U604.8 (GPB7)
unnamed: R625.1, U604.18 (RESET#)

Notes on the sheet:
ADC
CAN Tranceiver
Expanded High Active
Expanded Low Active
12V dio
CAN Controller
